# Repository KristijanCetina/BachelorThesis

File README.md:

# BachelorThesis

Završni rad stručnog studija Politehnike koji se izvodi pri [Istarskom Veleučilištu](https://www.iv.hr/)

Na sljedećem linku je dostupna [PDF verzija rada](https://github.com/KristijanCetina/BachelorThesis/blob/master/report/Zavr%C5%A1niRad-KristijanCetina.pdf)

Najlakši način za preuzeti ovaj rad ukoliko koristite git je putem sljedeće naredbe

``` bash
git clone https://github.com/KristijanCetina/BachelorThesis.git [<directory>]
```

pri čemu je `[<directory>]` neobavezan parameter - željeno ime projekta.

U suprotnom možete preuzeti cijeli kao .zip datoteku klikom na `Download`

## Summary

Prikupljanje, obrada i vizualizacija podataka nalazi se na svakom koraku našega života.
U ovom radu prikazan je postupak izrade snimača podataka koristeći Arduino platformu te obrada podataka koristeći isključivo alate otvorenog i slobodnog koda.
Hardwareska platforma trenutno koristi GPS prijemnik i temperaturni senzor te se u budućnosti planira povećanje broja senzora.
Podatci koji se skupljaju na uređaju spremaju se lokalno na memorijsku karticu ne bi li se kasnije analizirali na računalu pri čemu se koristi programski jezik Python unutar Jupyter notebook okruženja uz pomoć Pandas, NumPy i Matplotlib biblioteka.
Izrađeni alat za analizu radi na svim popularnim operacijskim sustavima danas u upotrebi.

U duhu otvorenog koda i dobre prakse znanstvene zajednice ovaj rad je napisan koristeći LaTeX sustav te je kompletan rad hostan na GitHub-u i slobodano dostupan svim zainteresiranim stranama koji žele nastaviti rad na ovoj temi.

### Ključne riječi

`Arduino, Python, Matplotlib, open-source, obrada podataka`

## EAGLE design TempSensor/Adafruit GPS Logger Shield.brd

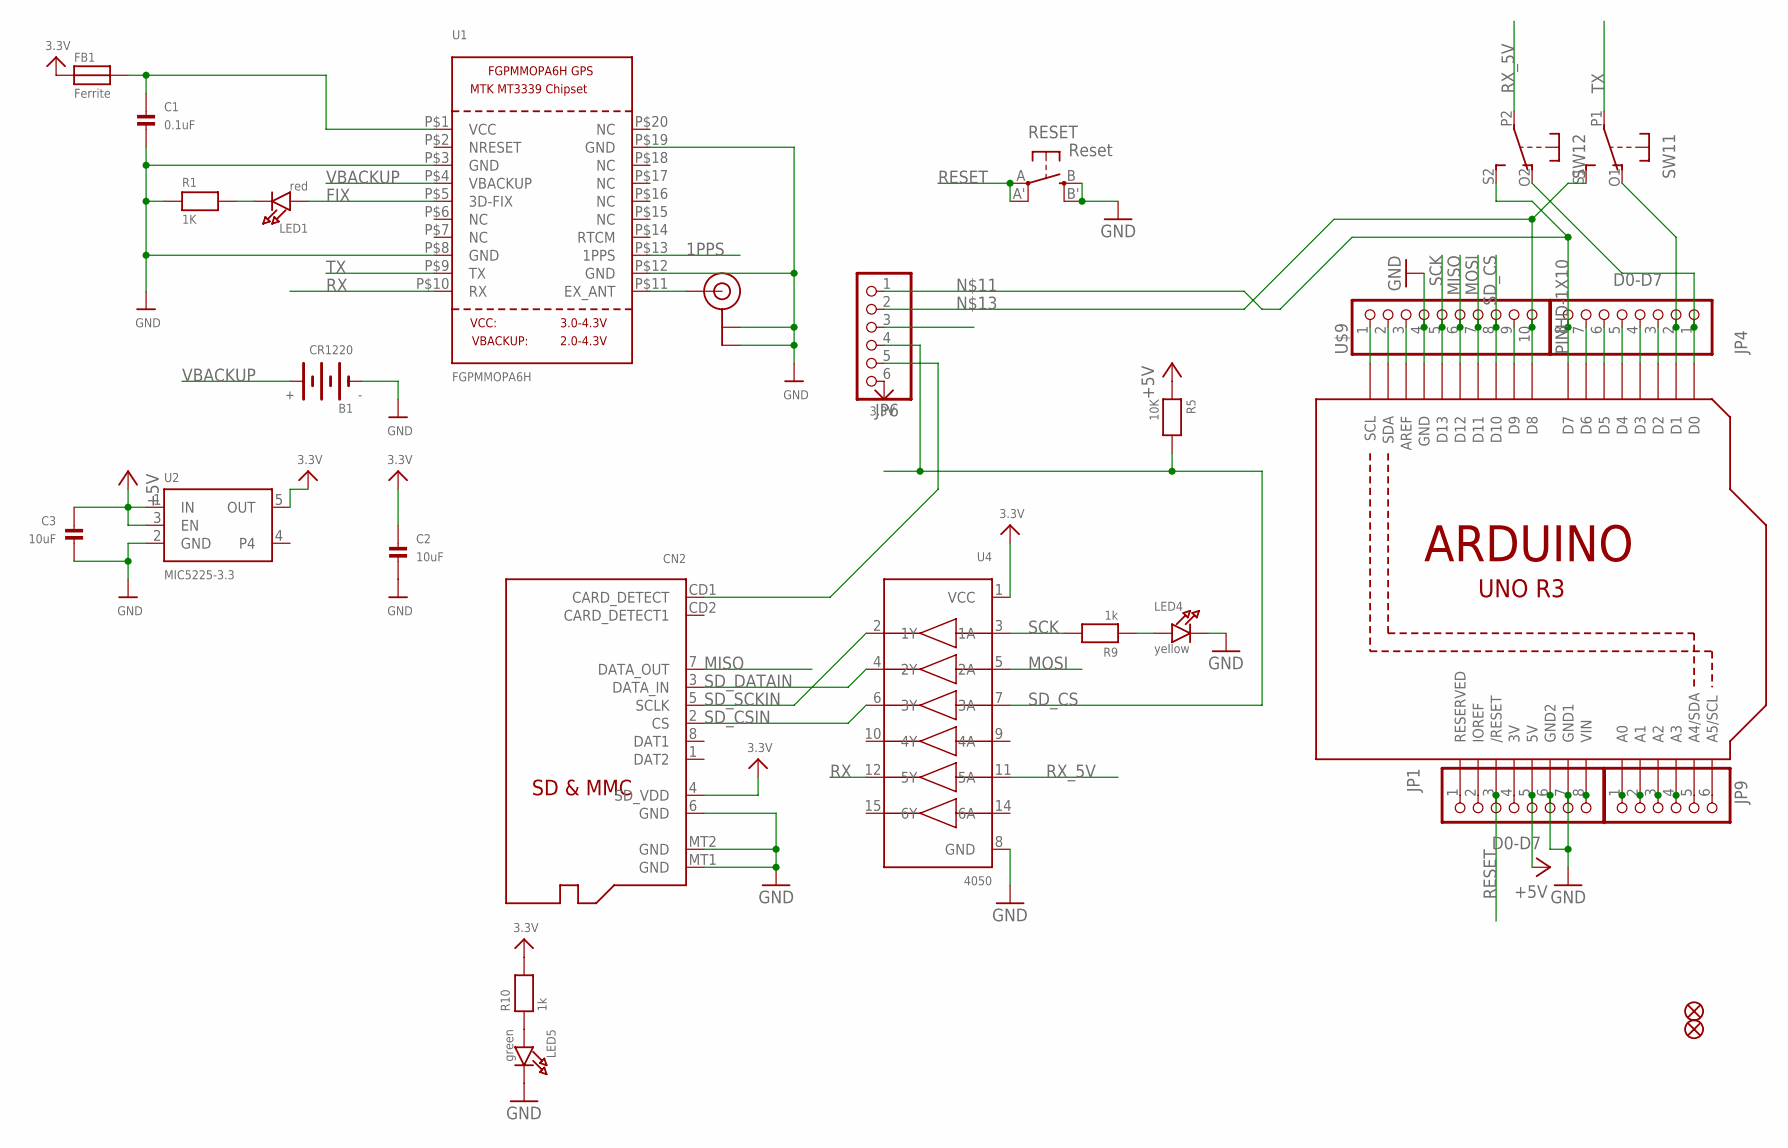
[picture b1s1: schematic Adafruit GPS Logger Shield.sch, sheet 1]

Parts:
B1: CR1220
C1: 0.1uF; 0805@1
C2, C3: 10uF; 0805@1
CN2: MICROSD
FB1: Ferrite; 0805@1
FID1, FID2: FIDUCIAL""; FIDUCIAL_1MM
JP1, JP4: D0-D7; 1X08-BIG
JP6, JP9: PINHD-1X6B; 1X06-BIG
LED1: red; CHIPLED_0805
LED4: yellow; CHIPLED_0805
LED5: green; CHIPLED_0805
R1: 1K; 0805
R5: 10K; 0805
R9, R10: 1k; 0805
RESET: Reset; EVQ-Q2
SW1: DPDT-EG1390; EG1390
U1: FGPMMOPA6H
U2: MIC5225-3.3; SOT23-5
U3: ARDUINOR3-DIMENSION; ARDUINOR3
U4: 4050; SOIC16
U$9: PINHD-1X10; 1X10-BIG
U$20: U.FL

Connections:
1PPS: JP6.3, U1.P$13 (1PPS)
3.3V: C2.1, CN2.4 (SD_VDD), FB1.1, JP6.6, R10.2, U2.5 (OUT), U4.1 (VCC)
+5V: C3.1, JP1.5, R5.1, U2.1 (IN), U2.3 (EN), U3.5V
FIX: LED1.A, U1.P$5 (3D-FIX)
GND: B1.-, C1.2, C2.2, C3.2, CN2.6 (GND), CN2.MT1 (GND), CN2.MT2 (GND), JP1.6, JP1.7, LED4.C, LED5.C, R1.1, RESET.B (S), RESET.B' (S1), U1.P$3 (GND), U1.P$8 (GND), U1.P$12 (GND), U1.P$19 (GND), U2.2 (GND), U3.GND, U3.GND1, U3.GND2, U4.8 (GND), U$9.4, U$20.P$1 (GND), U$20.P$2 (GND); also elsewhere on the board
MISO: CN2.7 (DATA_OUT), U3.D12, U$9.6
MOSI: U3.D11, U4.5 (2A), U$9.7
unnamed: C1.1, FB1.2, U1.P$1 (VCC)
unnamed: LED1.C, R1.2
unnamed: JP1.1, U3.RESERVED
unnamed: U1.P$11 (EX_ANT), U$20.P$3 (SIGNAL)
unnamed: JP1.2, U3.IOREF
unnamed: JP1.4, U3.3V
unnamed: U3.SCL, U$9.1
unnamed: LED4.A, R9.1
unnamed: JP9.6, U3.A5 (A5/SCL)
unnamed: JP9.5, U3.A4 (A4/SDA)
unnamed: JP4.8, JP6.1, SW1.S2 (S), U3.D7
unnamed: U3.SDA, U$9.2
unnamed: JP6.2, SW1.S1 (S), U3.D8, U$9.10
unnamed: JP4.2, SW1.O1 (O), U3.D1
unnamed: JP1.8, U3.VIN
unnamed: JP4.3, U3.D2
unnamed: JP4.4, U3.D3
unnamed: JP4.5, U3.D4
unnamed: JP4.6, U3.D5
unnamed: JP4.7, U3.D6
unnamed: U3.AREF, U$9.3
unnamed: U3.D9, U$9.9
unnamed: LED5.A, R10.1
unnamed 160: JP9.1, U3.A0; also elsewhere on the board
unnamed: JP9.2, U3.A1
unnamed: JP9.3, U3.A2
unnamed: JP9.4, U3.A3
unnamed: JP4.1, SW1.O2 (O), U3.D0
RESET: JP1.3, RESET.A, RESET.A' (P1), U3.RESET (/RESET)
RX: U1.P$10 (RX), U4.12 (5Y)
RX_5V: SW1.P2, U4.11 (5A)
SCK: R9.2, U3.D13, U4.3 (1A), U$9.5
SD_CD: CN2.CD1 (CARD_DETECT), JP6.5
SD_CS: JP6.4, R5.2, U3.D10, U4.7 (3A), U$9.8
SD_CSIN: CN2.2 (CS), U4.6 (3Y)
SD_DATAIN: CN2.3 (DATA_IN), U4.4 (2Y)
SD_SCKIN: CN2.5 (SCLK), U4.2 (1Y)
TX: SW1.P1, U1.P$9 (TX)
VBACKUP: B1.+$1 (+), U1.P$4 (VBACKUP)

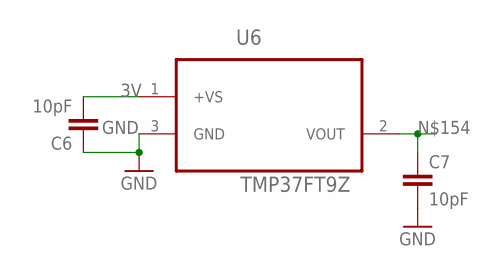
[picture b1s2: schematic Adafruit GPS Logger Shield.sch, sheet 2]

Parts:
C6, C7: 10pF; C2.5-3
U6: TMP37FT9Z; TO254P508X660-3P

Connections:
3V: C6.2, U6.1 (+VS)
GND: C6.1, C7.2, U6.3 (GND); also elsewhere on the board
unnamed 160: C7.1, U6.2 (VOUT); also elsewhere on the board

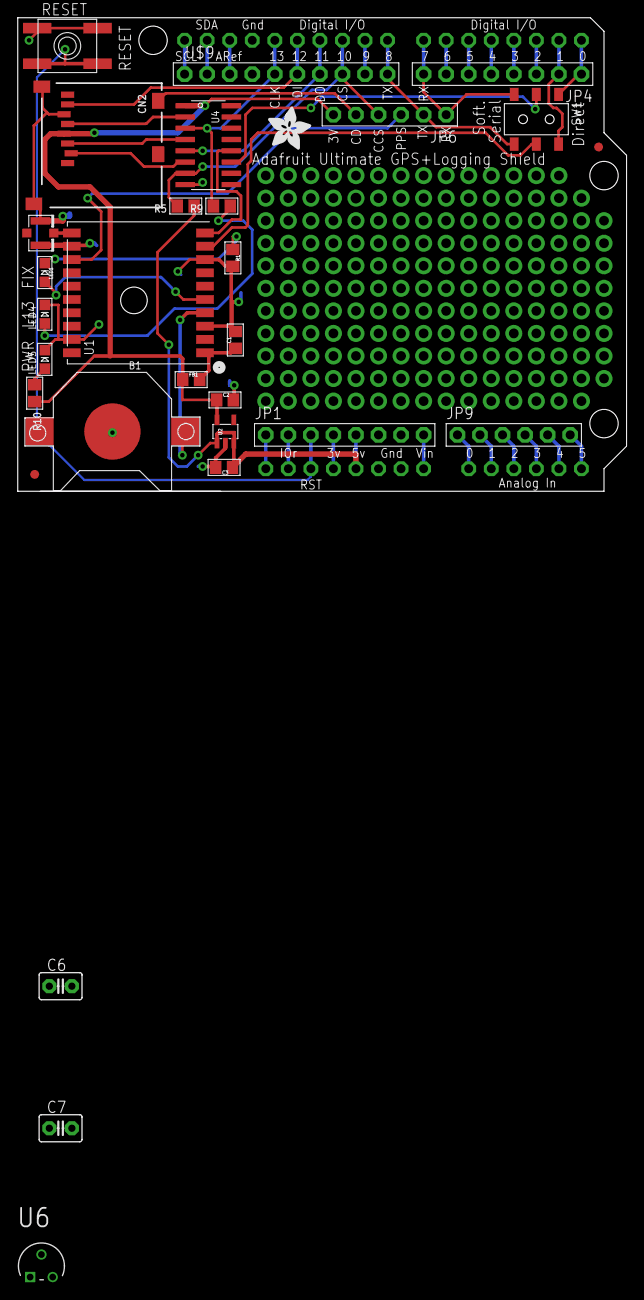
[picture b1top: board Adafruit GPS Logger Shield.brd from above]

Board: 2 copper layers, 68.6 x 53.3 mm, 32 parts (1 on the bottom side), 47 nets.

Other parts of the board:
U$13: ADAFRUIT_5MM
U$15: ADAFRUIT_TEXT_30MM

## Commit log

2019-03-28 init commit
2019-03-28 template
2019-03-30 added hw test sourcecode
2019-04-04 formating
2019-04-08 Update LoggingWithTemp.ino
    Za sada dela nekako
2019-04-17 dodana poglavlja - struktura rada
2019-05-04 sredivanje
2019-05-05 Slaganje strukture
2019-05-27 Prijava i naziv teme
2019-07-18 added adafruit GPS shield files
2019-07-18 added TMP36 circuitry
2019-07-19 dodane sitnice u sw
2019-07-25 testing logger_temp + gps
2019-07-25 Dodan TMP36 datasheet u repo
2019-08-03 Uvod, AboutOpenSource
2019-08-03 formatting
2019-08-05 Create HardwareSetup.jpg
    Dodana
2019-08-07 Added data sources
2019-08-08 nastavak na uvodu, mini reorganizacija
2019-08-12 dodatak Jupyter
2019-08-18 malo o hardwareu
2019-08-18 eagleBackup file handling
2019-08-18 added Jupyter notebook
2019-08-21 AboutTempSensor
2019-08-21 Prevent hyphenation of some words
2019-08-24 data acquisition
2019-08-24 minor update
2019-08-25 dodan naziv rada u Izjavu, Analiza podataka u toku
2019-08-25 analiza dela
2019-08-25 analizaPodataka_workInProgress
2019-08-25 za prvi pregled
2019-08-27 update Readme.md - clone or download
2019-08-27 readme.md pic display
2019-08-27 colorcoded command
2019-08-27 Odvojen uvod, promjenjena numeracija
2019-08-27 added peek-to-peek temp
2019-08-28 dodan two scale plot
2019-08-28 work in progress
2019-08-29 Još malo o JupyterNotebook
2019-08-29 added legends to graphs
2019-08-31 gramatičke ispravke
2019-09-03 dodan scatter plot pozicije
2019-09-03 update analiza
2019-09-04 rename folder LaTeX -> report, added text to intro
2019-09-05 dodan put lifta
2019-09-05 posveta, zahvala i sažetak
2019-09-05 sitne ispravke
2019-09-06 sommario aggiunto
2019-09-06 dodan koordinatni sustav phyphox
2019-09-06 sommario
2019-09-07 one-sided report config
2019-09-07 grammar
2019-09-07 added new datasource
2019-09-07 Summary order
2019-09-08 Added presentation v_0.1
2019-09-11 no hyphenation
2019-09-12 lektura - part1
    Sorry Martina što si ovo morala čitati :-)
2019-09-14 lektura - part2
2019-09-14 macOS test
2019-09-14 recompiled
2019-09-16 početne stranice, popis oznaka
    Dodane željene početne stranice, iskomentiran {titlepage}, dodan popis oznaka i kratica, sažeci u poseban .tex
2019-09-17 fali 't' u footnote
2019-09-17 završne ispravke
2019-10-22 Revert ".."
    This reverts commit 6edd6d0c517a2bf49eea0791396ac42988ef0014.
2019-10-22 Revert "."
    This reverts commit dec3cde70e271dc5411f8a55643094883e71ac28.
2019-10-22 cleanUp
2019-11-25 Update issue templates
